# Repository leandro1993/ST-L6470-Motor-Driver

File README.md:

# ST-L6470-Motor-Driver
Single Motor stepper driver module using ST L6470

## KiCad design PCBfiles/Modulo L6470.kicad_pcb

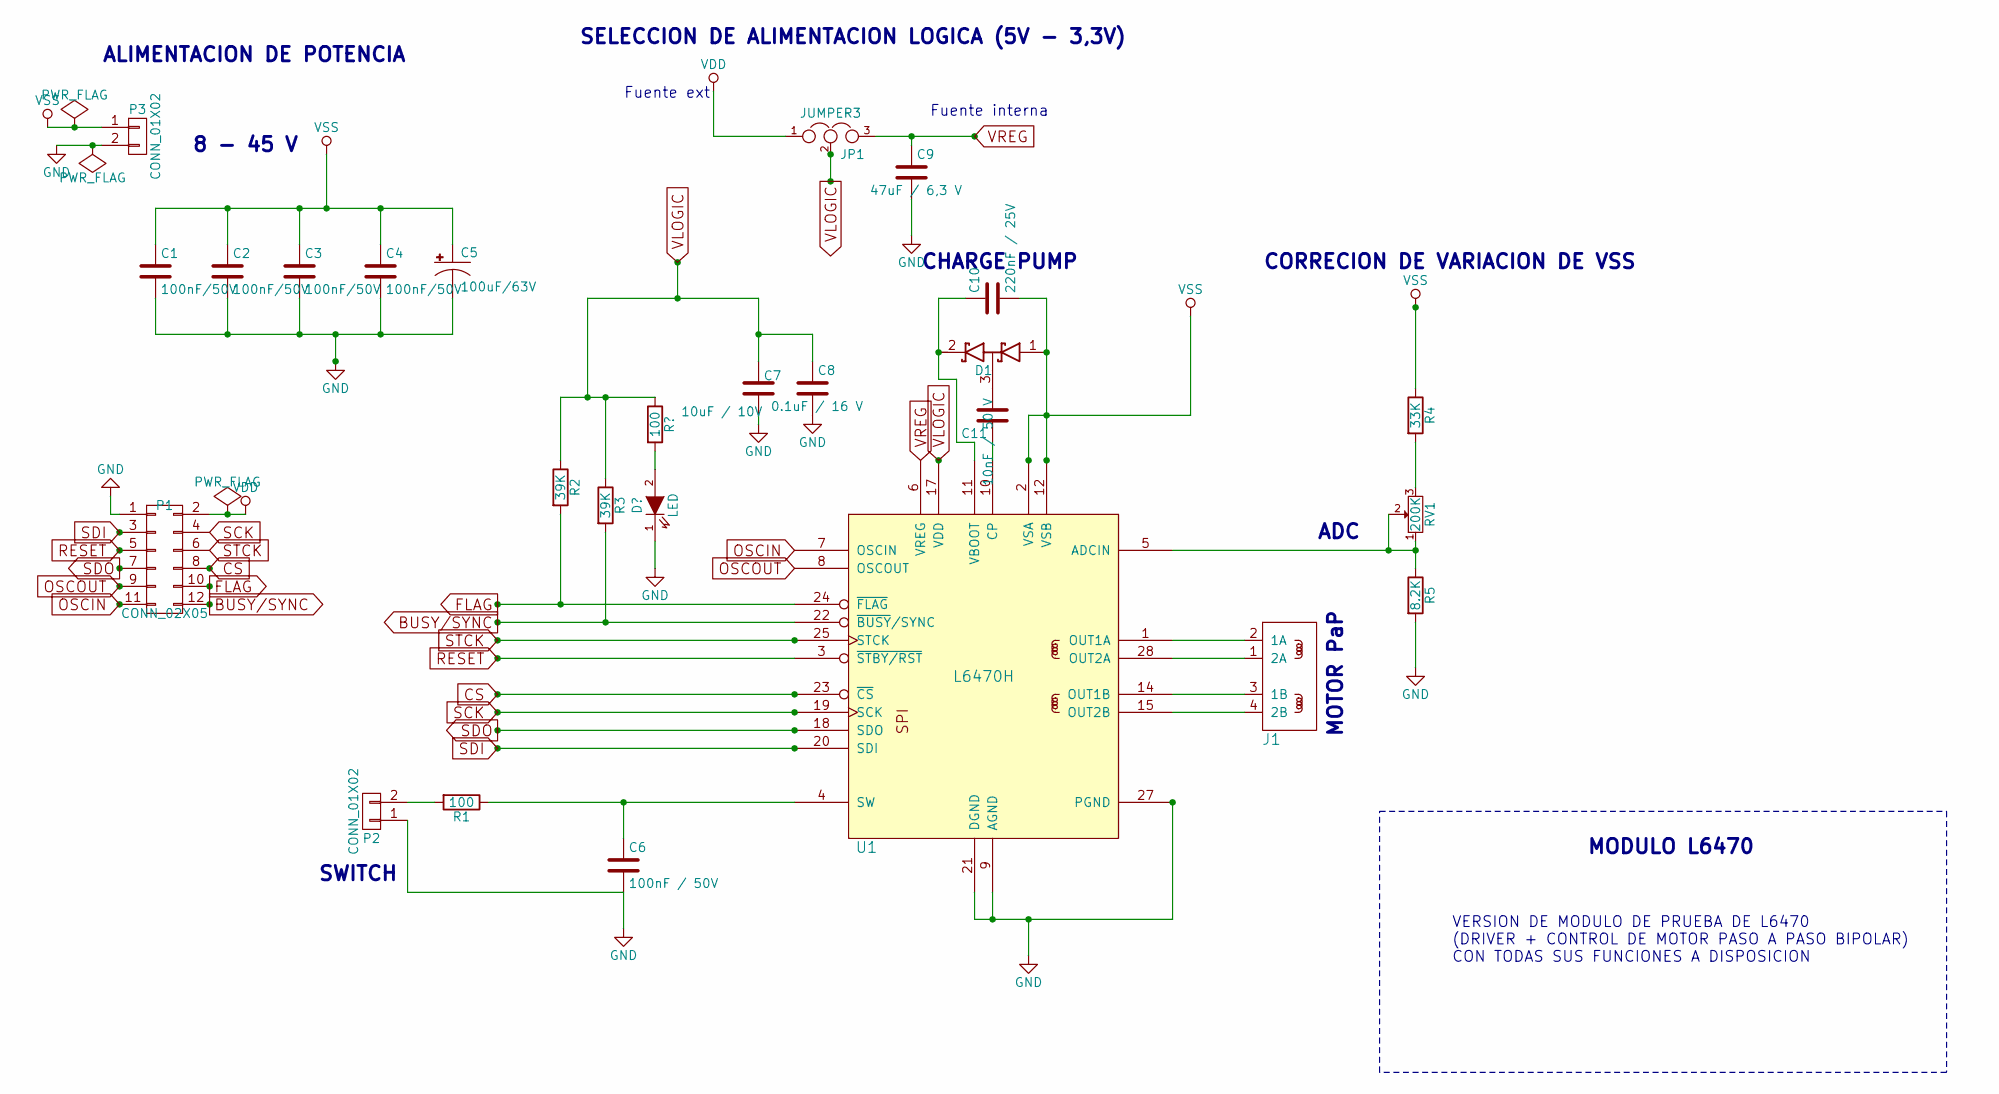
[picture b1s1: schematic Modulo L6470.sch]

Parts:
C1, C2, C3, C4: 100nF/50V; C_0603
C5: 100uF/63V; PANASONIC_H13
C6: 100nF / 50V; C_0603
C7: 10uF / 10V; C_1206
C8: 0.1uF / 16 V; C_0603
C9: 47uF / 6,3 V; C_0805
C10: 220nF / 25V; C_0603
C11: 10nF / 50 V; C_0603
D1: D_Schottky_x2_Serial_CAK; SOT-23
J1: CONN_STEPPER; TerminalBlock_Pheonix_MKDS1.5-4pol
JP1: JUMPER3; Pin_Header_Straight_1x03
P1: CONN_02X05; Pin_Header_Straight_2x06
P2, P3: CONN_01X02; TerminalBlock_Pheonix_MKDS1.5-2pol
R1: 100; R_0603
R2, R3: 39K; R_0603
R4: 33K; R_0603
R5: 8.2K; R_0603
RV1: 200K; Potentiometer_WirePads_Small
U1: L6470H; tssop-28-pwp

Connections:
BUSY/SYNC: P1.12, R3.2, U1.22 (~BUSY~/SYNC)
CS: P1.8, U1.23 (~CS)
FLAG: P1.10, R2.2, U1.24 (~FLAG)
GND: C1.2, C2.2, C3.2, C4.2, C5.-, C6.2, C7.2, C8.2, C9.2, P1.1, P2.1, P3.2, R5.2, U1.9 (AGND), U1.13 (PGND), U1.21 (DGND), U1.27 (PGND), U1.PAD (PGND)
unnamed: C6.1, R1.1, U1.4 (SW)
unnamed: C10.1, D1.2 (K), U1.11 (VBOOT)
unnamed: C11.1, U1.10 (CP)
unnamed: C11.2, D1.3 (common)
unnamed: J1.1 (2A), U1.28 (OUT2A)
unnamed: J1.2 (1A), U1.1 (OUT1A)
unnamed: J1.3 (1B), U1.14 (OUT1B)
unnamed: J1.4 (2B), U1.15 (OUT2B)
unnamed: P2.2, R1.2
unnamed: R4.2, RV1.3
unnamed: R5.1, RV1.1, RV1.2, U1.5 (ADCIN)
OSCIN: P1.11, U1.7 (OSCIN)
OSCOUT: P1.9, U1.8 (OSCOUT)
RESET: P1.5, U1.3 (~STBY/RST)
SCK: P1.4, U1.19 (SCK)
SDI: P1.3, U1.20 (SDI)
SDO: P1.7, U1.18 (SDO)
STCK: P1.6, U1.25 (STCK)
VDD: JP1.1, P1.2
VLOGIC: C7.1, C8.1, JP1.2, R2.1, R3.1, U1.17 (VDD)
VREG: C9.1, JP1.3, U1.6 (VREG)
VSA: C1.1, C2.1, C3.1, C4.1, C5.+, C10.2, D1.1 (A), P3.1, R4.1, U1.2 (VSA), U1.12 (VSB), U1.16 (VSB), U1.26 (VSA)

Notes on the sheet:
VERSION DE MODULO DE PRUEBA DE L6470 (DRIVER + CONTROL DE MOTOR PASO A PASO BIPOLAR) CON TODAS SUS FUNCIONES A DISPOSICION
MODULO L6470
ALIMENTACION DE POTENCIA
8 - 45 V
SELECCION DE ALIMENTACION LOGICA (5V - 3,3V)
SWITCH
CHARGE PUMP
CORRECION DE VARIACION DE VSS
ADC
MOTOR PaP
Fuente ext
Fuente interna

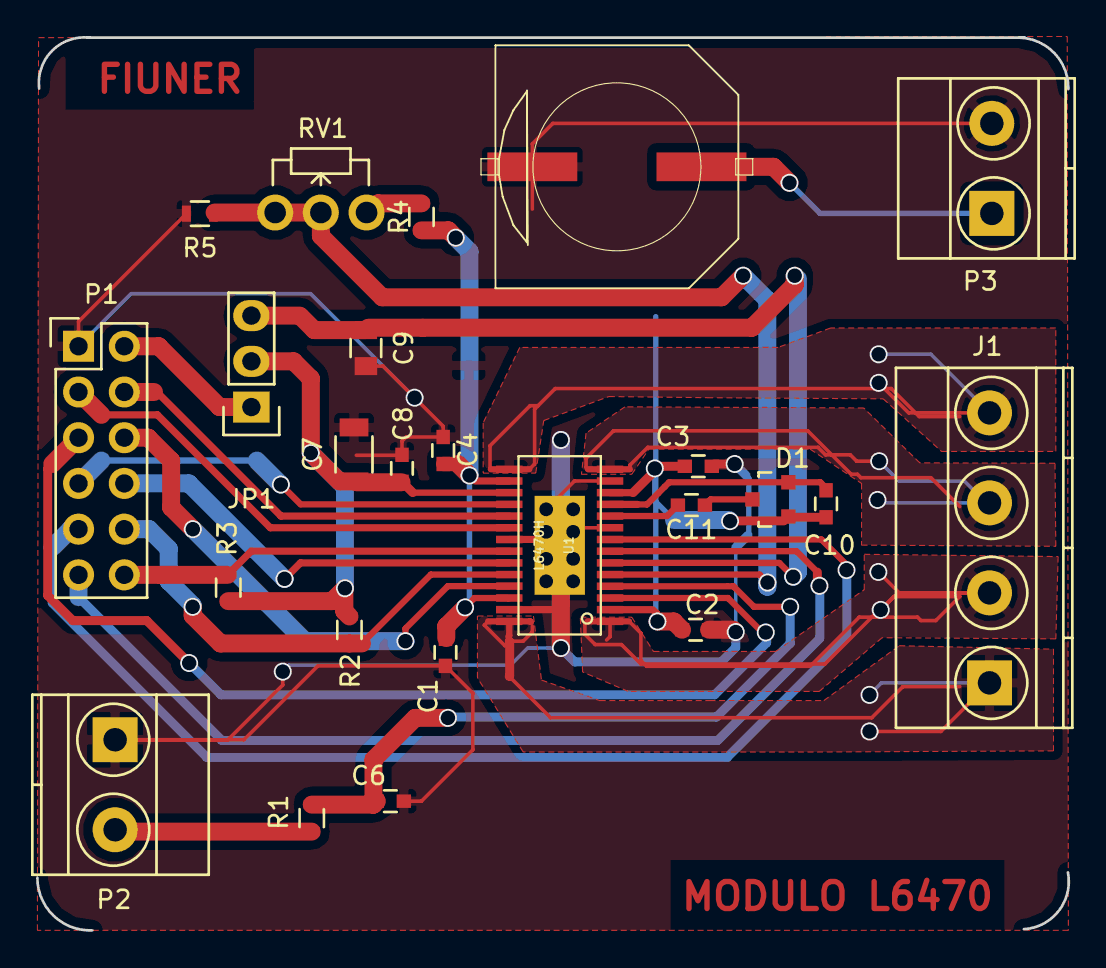
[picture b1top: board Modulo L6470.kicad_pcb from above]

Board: 2 copper layers, 57.3 x 49.6 mm, 24 parts (0 on the bottom side), 26 nets.

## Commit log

2018-10-18 Code files added
2018-10-18 schematic file added
2018-10-18 PCB files added
2018-10-18 Upload license
